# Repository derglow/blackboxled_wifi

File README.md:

# blackboxled_wifi
PCB design and esphome code to connect black box LEDs to WiFi.

The PCB serves two functions...
1) Connect 3.3V digital output to transistor to toggle lights on/off
2) Convert 3.3V PWM into a 0-10V analog output

Parts list:
1) NodeMCU - $4
2) 12V Power Supply - $5
3) PCB - $4

Rough Cost - $13 + a few bucks for components

Link to order the PCBs ($11 for 3):
https://oshpark.com/shared_projects/AcYhgbWN

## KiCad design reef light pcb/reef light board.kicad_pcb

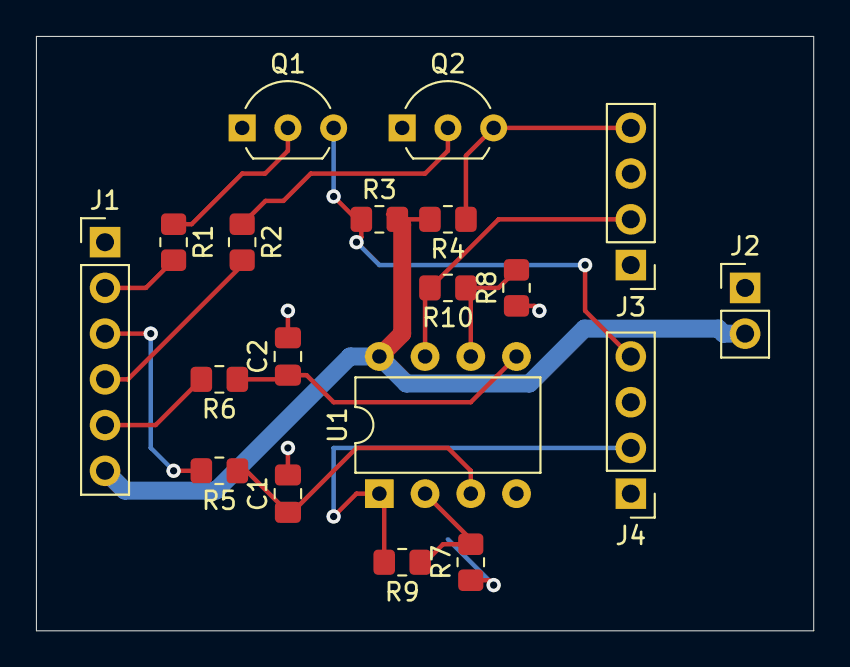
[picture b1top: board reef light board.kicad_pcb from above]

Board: 2 copper layers, 43.2 x 33.0 mm, 19 parts (0 on the bottom side), 16 nets.

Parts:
C1, C2: 1uF; C_0805_2012Metric_Pad1.18x1.45mm_HandSolder
J1: Conn_01x06_Male; PinHeader_1x06_P2.54mm_Vertical
J2: Conn_01x02_Male; PinHeader_1x02_P2.54mm_Vertical
J3, J4: Conn_01x04_Male; PinHeader_1x04_P2.54mm_Vertical
Q1, Q2: Q_NPN_EBC; TO-92L_Inline_Wide
R1, R2: 3000; R_0805_2012Metric_Pad1.20x1.40mm_HandSolder
R3, R4: 8k; R_0805_2012Metric_Pad1.20x1.40mm_HandSolder
R5: 100K; R_0805_2012Metric_Pad1.20x1.40mm_HandSolder
R6: 100k; R_0805_2012Metric_Pad1.20x1.40mm_HandSolder
R7, R8: 1k; R_0805_2012Metric_Pad1.20x1.40mm_HandSolder
R9, R10: 2.2k; R_0805_2012Metric_Pad1.20x1.40mm_HandSolder
U1: LM358; DIP-8_W7.62mm

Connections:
+12V: J1.6, J2.2, R3.2, R4.2, U1.8
GND: C1.2, C2.2, J1.1, J2.1, J3.1, J4.1, Q1.1, Q2.1, R7.1, R8.1, U1.4
L1OnOff3.3V: J1.2, R1.2
L1OnOff12V: J4.4, Q1.3, R3.1
L1_0-10_Analog: J4.2, R9.2, U1.1
L1_PWM: J1.3, R5.2
L2OnOff3.3V: J1.4, R2.2
L2OnOff12V: J3.4, Q2.3, R4.1
L2_0-10_Analog: J3.2, R10.2, U1.7
L2_PWM: J1.5, R6.2
unnamed: C1.1, R5.1, U1.3
unnamed: C2.1, R6.1, U1.5
unnamed: Q1.2, R1.1
unnamed: Q2.2, R2.1
unnamed: R7.2, R9.1, U1.2
unnamed: R8.2, R10.1, U1.6

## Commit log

2020-11-15 initial uploading of kicad and yaml
2020-11-15 adding images for readme
